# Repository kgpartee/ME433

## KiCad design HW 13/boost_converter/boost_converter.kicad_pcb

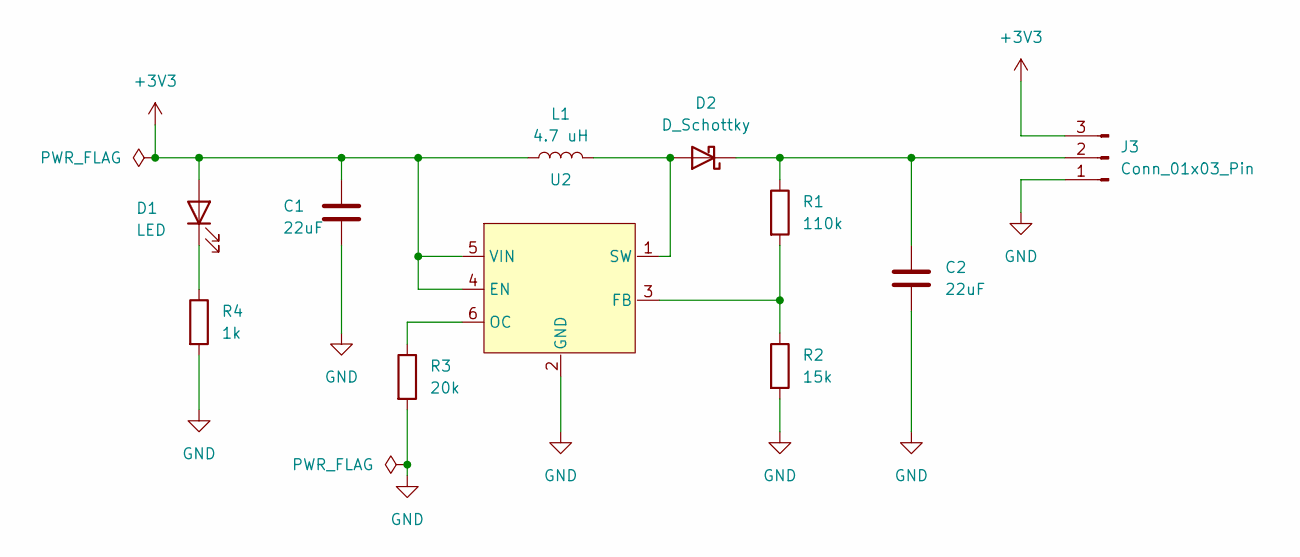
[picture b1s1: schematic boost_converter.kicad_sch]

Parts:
C1, C2: 22uF; C_0603_1608Metric
D1: LED; LED_0805_2012Metric
D2: D_Schottky; D_SOD-123
J3: Conn_01x03_Pin; PinHeader_1x03_P2.54mm_Vertical
L1: 4.7 uH; L_0603_1608Metric
R1: 110k; R_0603_1608Metric
R2: 15k; R_0603_1608Metric
R3: 20k; R_0603_1608Metric
R4: 1k; R_0603_1608Metric
U2: SOT-23-6

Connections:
+3V3: C1.1, D1.2 (A), J3.3, L1.1, U2.4 (EN), U2.5 (VIN)
GND: C1.2, C2.2, J3.1, R2.2, R3.2, R4.2, U2.2 (GND)
unnamed: D1.1 (K), R4.1
unnamed: D2.2 (A), L1.2, U2.1 (SW)
unnamed: C2.1, D2.1 (K), J3.2, R1.1
unnamed: R1.2, R2.1, U2.3 (FB)
unnamed: R3.1, U2.6 (OC)

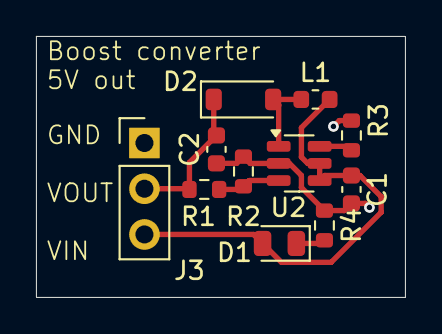
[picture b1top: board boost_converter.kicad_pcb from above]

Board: 2 copper layers, 20.5 x 14.5 mm, 11 parts (0 on the bottom side), 7 nets.

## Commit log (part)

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2026-04-02 created pico project
2026-04-03 set up pwm
2026-04-03 wrote set servo function
2026-04-06 added servo sweep to while loop
2026-04-06 wrote python code
2026-04-06 tuned angles
2026-04-06 tuned python angles
2026-04-06 tuned angles in c
2026-04-07 initialized pico project
2026-04-07 init finctions and read pin
2026-04-07 set pin function
2026-04-07 blink LED with expander
2026-04-07 button press
2026-04-09 made pico project
2026-04-09 added sample code
2026-04-10 display functions h and c file
2026-04-10 pixel blinking
2026-04-10 sprintf message
2026-04-10 fps printing
2026-04-14 initialized pi project, imported files to write to display
2026-04-15 initialize i2c
2026-04-15 tested buf value
2026-04-15 init and read functions
2026-04-15 read and recombination functions
2026-04-16 screen printing code
2026-04-16 downloaded usb example code
2026-04-16 set to mouse device
2026-04-23 mouse moves in circle
2026-04-23 make hw 8 project, in class pseudo code
2026-04-30 used ai tool to make game
2026-04-30 wrote pico code to read button and potentiometer
2026-04-30 fixed serial port connection
2026-04-30 imported smaple code/files
2026-04-30 added csv reading to fft
2026-05-01 iir filter
2026-05-01 fir filter
2026-05-05 initialized stm project
2026-05-15 Schematic and PCB design
2026-05-19 initialize hw 14
2026-05-23 hw 11- hello world printing
2026-05-23 uart in stm
2026-05-23 initialized pico uart
2026-05-27 debug uart communication
2026-05-28 updated spi dac functions
2026-06-03 finished ram and dac
2026-06-09 finsihed 16
2026-06-09 added files for 16
2026-06-09 photo of 3d prints for 15
2026-06-09 initialized encoder code
2026-06-09 added graphics to encoder sensing
2026-06-09 hw 14 code
2026-06-09 collected plots for force sensor
2026-06-09 graphs for 18
2026-06-10 made final project code folder
2026-06-10 moved other assignments over as libraries
2026-06-10 done
2026-06-10 added functional videos
